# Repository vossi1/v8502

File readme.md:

# V8502 - Replacement for a 8502 with a 6502  

**Copyright (c) 2024 Vossi - v.1**

**www.mos6502.net**

## License
This work is licensed under a Creative Commons Attribution-ShareAlike 4.0
International License. See [https://creativecommons.org/licenses/by-sa/4.0/](https://creativecommons.org/licenses/by-sa/4.0/).

v.1 initial (base is V6510 v.3)

**[Schematic](https://github.com/vossi1/v8502/blob/master/v8502_v1.png)**

**[Parts](https://github.com/vossi1/v8502/blob/master/parts.txt)**

**CPLD-Firmware:** The .JED file can be uploaded with a JTAG-SMT2 Xilinx programmer (China) and [xc3sprog](https://xc3sprog.sourceforge.net/)

:exclamation: **BEWARE: I got good CPLD's from China, but there are some XC9572XL FAKES out there!**

:white_check_mark: **Tested successfully  with a UMC 6502A in my C128 & C128D-CR::**

- Risen from the Oblivion VIC
- Risen from the Oblivion VDC
- CPM VIC mode
- CPM VDC 80 column mode
- GEOS VIC mode with REU 1764, Mouse
- GEOS VDC mode with REU 1764, Mouse
- C128 Diagnostic cartridge
- Elite 128
- Sonic with REU 1764 c64 mode
- Galaxian cartridge C64 mode
- Blue Max from disk C64 mode
- Basic lesson loaded from tape
- SD2IEC with FB64 & FB128

**For a WDC 65C02 you have to cut the small trace in the other solder jumper.**

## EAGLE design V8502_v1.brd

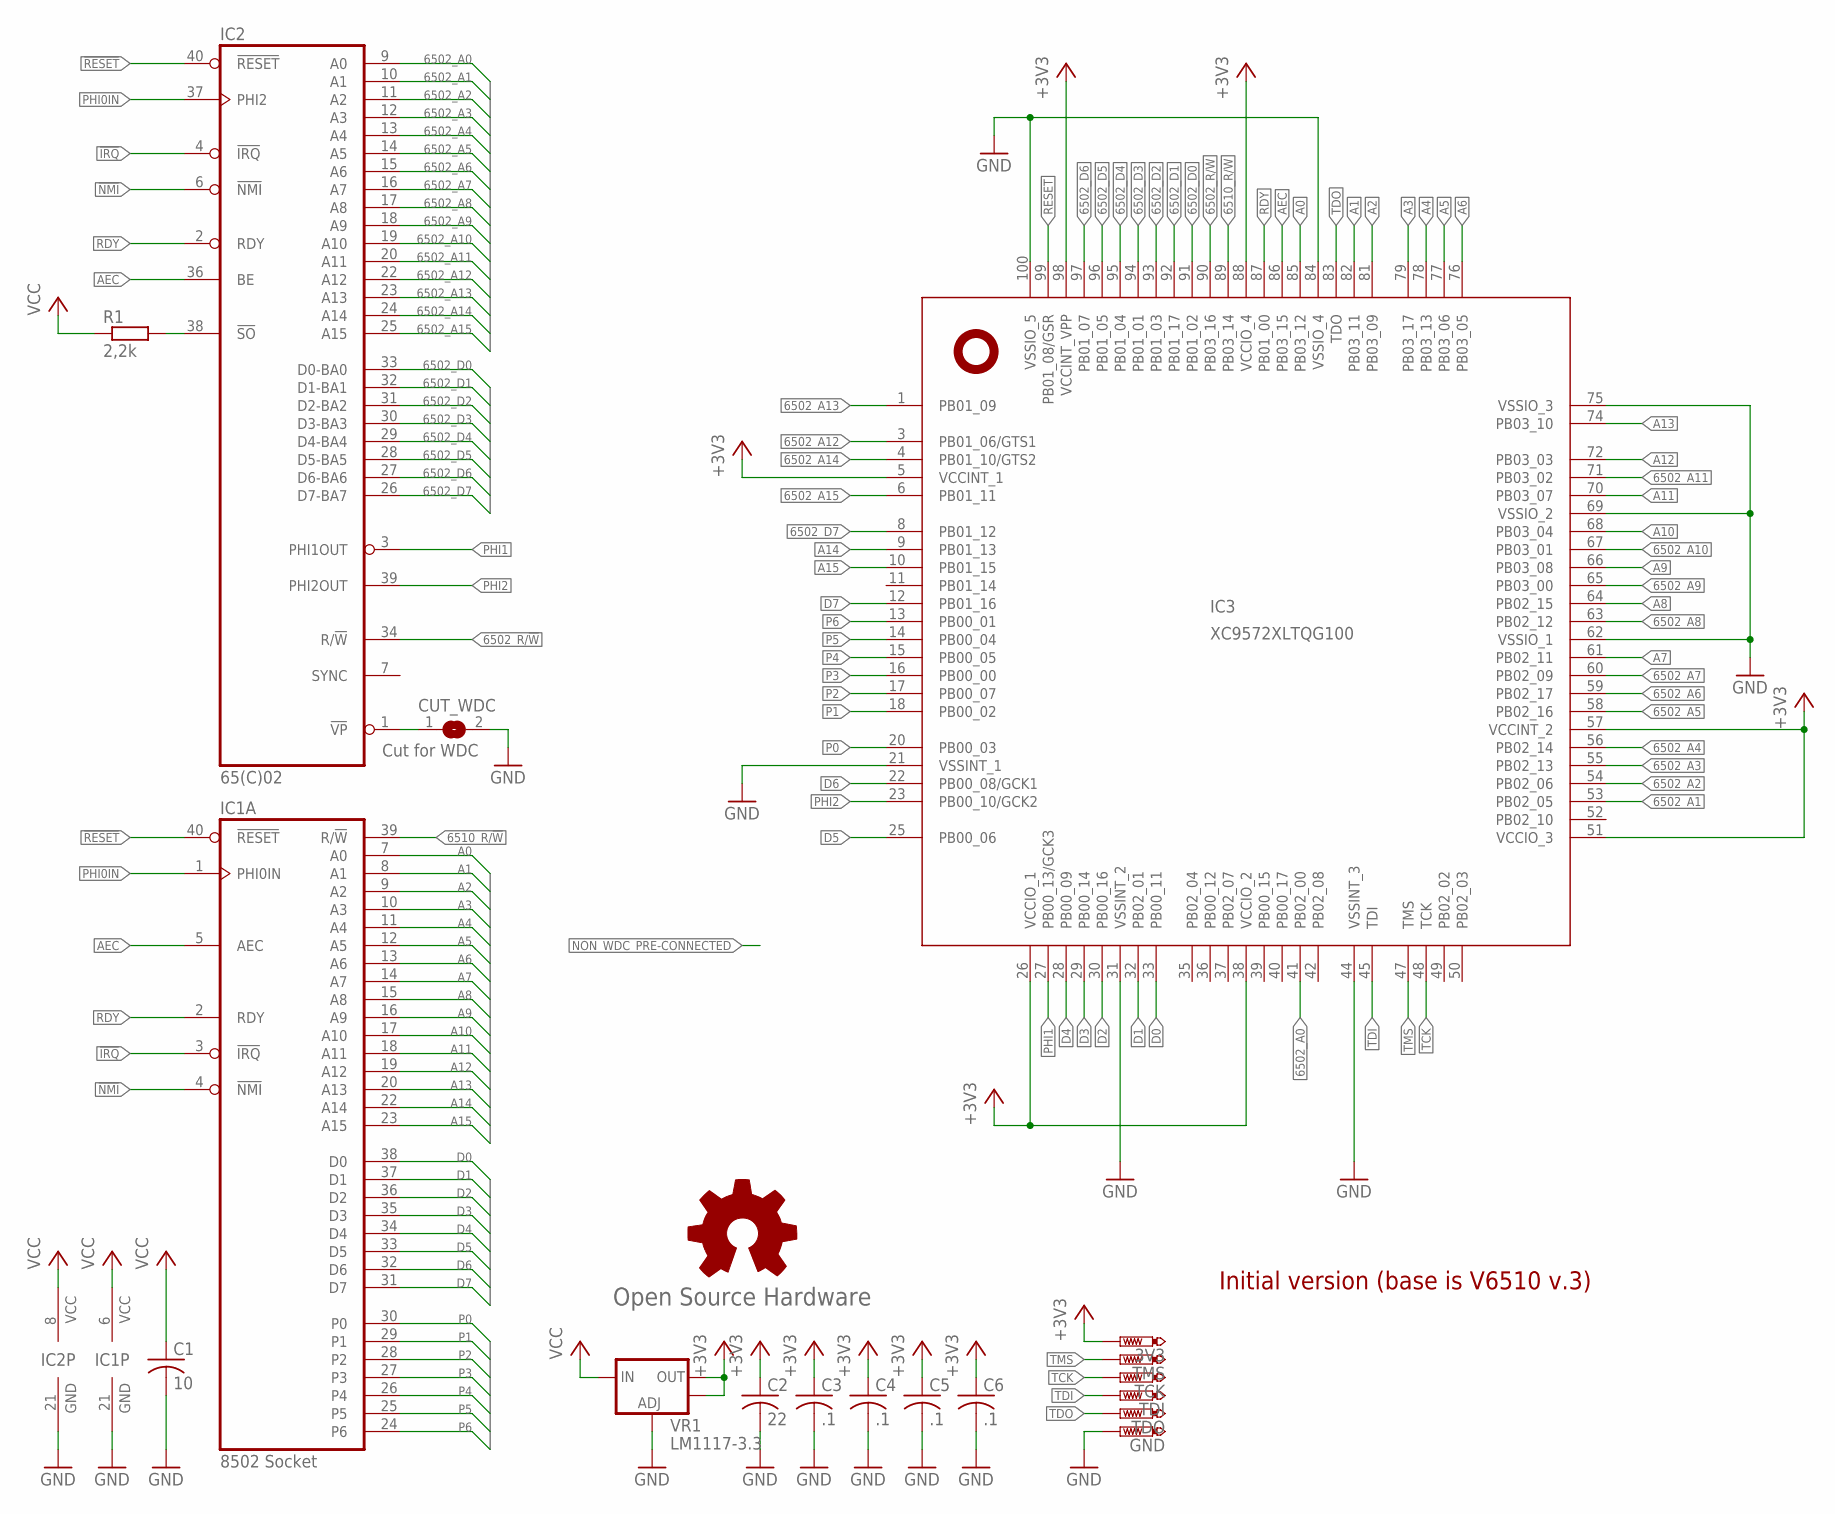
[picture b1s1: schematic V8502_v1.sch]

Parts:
3V3: PTR1TP08R; TP08R
C1: 10; C0805
C2: 22; C0805
C3, C4, C5, C6: .1; C0603
CUT_WDC: Cut for WDC; SJ
GND: PTR1TP08R; TP08R
GOLD_ORB_SM1: Open Source Hardware; OSHW_5MM
IC1: 8502 Socket; DIL40-ROUNDPAD
IC2: 65(C)02; DIL40-ROUNDPAD
IC3: XC9572XLTQG100; TQFP100
R1: 2,2k; 0603
TCK: PTR1TP08R; TP08R
TDI: PTR1TP08R; TP08R
TDO: PTR1TP08R; TP08R
TMS: PTR1TP08R; TP08R
VR1: LM1117-3.3; SOT223

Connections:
6502_A0: IC2.9 (A0), IC3.41 (PB02_00)
6502_A1: IC2.10 (A1), IC3.53 (PB02_05)
6502_A2: IC2.11 (A2), IC3.54 (PB02_06)
6502_A3: IC2.12 (A3), IC3.55 (PB02_13)
6502_A4: IC2.13 (A4), IC3.56 (PB02_14)
6502_A5: IC2.14 (A5), IC3.58 (PB02_16)
6502_A6: IC2.15 (A6), IC3.59 (PB02_17)
6502_A7: IC2.16 (A7), IC3.60 (PB02_09)
6502_A8: IC2.17 (A8), IC3.63 (PB02_12)
6502_A9: IC2.18 (A9), IC3.65 (PB03_00)
6502_A10: IC2.19 (A10), IC3.67 (PB03_01)
6502_A11: IC2.20 (A11), IC3.71 (PB03_02)
6502_A12: IC2.22 (A12), IC3.3 (PB01_06/GTS1)
6502_A13: IC2.23 (A13), IC3.1 (PB01_09)
6502_A14: IC2.24 (A14), IC3.4 (PB01_10/GTS2)
6502_A15: IC2.25 (A15), IC3.6 (PB01_11)
6502_D0: IC2.33 (D0-BA0), IC3.91 (PB01_02)
6502_D1: IC2.32 (D1-BA1), IC3.92 (PB01_17)
6502_D2: IC2.31 (D2-BA2), IC3.93 (PB01_03)
6502_D3: IC2.30 (D3-BA3), IC3.94 (PB01_01)
6502_D4: IC2.29 (D4-BA4), IC3.95 (PB01_04)
6502_D5: IC2.28 (D5-BA5), IC3.96 (PB01_05)
6502_D6: IC2.27 (D6-BA6), IC3.97 (PB01_07)
6502_D7: IC2.26 (D7-BA7), IC3.8 (PB01_12)
6502_R/!W: IC2.34 (R/!W), IC3.90 (PB03_16)
6502_VSS: CUT_WDC.1, IC2.1 (!VP)
6510_R/!W: IC1.39 (R/!W), IC3.89 (PB03_14)
!IRQ: IC1.3 (!IRQ), IC2.4 (!IRQ)
!NMI: IC1.4 (!NMI), IC2.6 (!NMI)
!RESET: IC1.40 (!RESET), IC2.40 (!RESET), IC3.99 (PB01_08/GSR)
!SO: IC2.38 (!SO), R1.2
+3V3: 3V3.TP, C2.1, C3.1, C4.1, C5.1, C6.1, IC3.5 (VCCINT_1), IC3.26 (VCCIO_1), IC3.38 (VCCIO_2), IC3.51 (VCCIO_3), IC3.57 (VCCINT_2), IC3.88 (VCCIO_4), IC3.98 (VCCINT_VPP), VR1.2 (OUT), VR1.4 (OUT)
A0: IC1.7 (A0), IC3.85 (PB03_12)
A1: IC1.8 (A1), IC3.82 (PB03_11)
A2: IC1.9 (A2), IC3.81 (PB03_09)
A3: IC1.10 (A3), IC3.79 (PB03_17)
A4: IC1.11 (A4), IC3.78 (PB03_13)
A5: IC1.12 (A5), IC3.77 (PB03_06)
A6: IC1.13 (A6), IC3.76 (PB03_05)
A7: IC1.14 (A7), IC3.61 (PB02_11)
A8: IC1.15 (A8), IC3.64 (PB02_15)
A9: IC1.16 (A9), IC3.66 (PB03_08)
A10: IC1.17 (A10), IC3.68 (PB03_04)
A11: IC1.18 (A11), IC3.70 (PB03_07)
A12: IC1.19 (A12), IC3.72 (PB03_03)
A13: IC1.20 (A13), IC3.74 (PB03_10)
A14: IC1.22 (A14), IC3.9 (PB01_13)
A15: IC1.23 (A15), IC3.10 (PB01_15)
AEC: IC1.5 (AEC), IC2.36 (BE), IC3.86 (PB03_15)
D0: IC1.38 (D0), IC3.33 (PB00_11)
D1: IC1.37 (D1), IC3.32 (PB02_01)
D2: IC1.36 (D2), IC3.30 (PB00_16)
D3: IC1.35 (D3), IC3.29 (PB00_14)
D4: IC1.34 (D4), IC3.28 (PB00_09)
D5: IC1.33 (D5), IC3.25 (PB00_06)
D6: IC1.32 (D6), IC3.22 (PB00_08/GCK1)
D7: IC1.31 (D7), IC3.12 (PB01_16)
GND: C1.2, C2.2, C3.2, C4.2, C5.2, C6.2, CUT_WDC.2, GND.TP, IC1.21 (GND), IC2.21 (GND), IC3.21 (VSSINT_1), IC3.31 (VSSINT_2), IC3.44 (VSSINT_3), IC3.62 (VSSIO_1), IC3.69 (VSSIO_2), IC3.75 (VSSIO_3), IC3.84 (VSSIO_4), IC3.100 (VSSIO_5), VR1.1 (ADJ)
P0: IC1.30 (P0), IC3.20 (PB00_03)
P1: IC1.29 (P1), IC3.18 (PB00_02)
P2: IC1.28 (P2), IC3.17 (PB00_07)
P3: IC1.27 (P3), IC3.16 (PB00_00)
P4: IC1.26 (P4), IC3.15 (PB00_05)
P5: IC1.25 (P5), IC3.14 (PB00_04)
P6: IC1.24 (P6), IC3.13 (PB00_01)
PHI0IN: IC1.1 (PHI0IN), IC2.37 (PHI2)
PHI1: IC2.3 (PHI1OUT), IC3.27 (PB00_13/GCK3)
PHI2: IC2.39 (PHI2OUT), IC3.23 (PB00_10/GCK2)
RDY: IC1.2 (RDY), IC2.2 (RDY), IC3.87 (PB01_00)
TCK: IC3.48 (TCK), TCK.TP
TDI: IC3.45 (TDI), TDI.TP
TDO: IC3.83 (TDO), TDO.TP
TMS: IC3.47 (TMS), TMS.TP
VCC: C1.1, IC1.6 (VCC), IC2.8 (VCC), R1.1, VR1.3 (IN)

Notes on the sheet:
Initial version (base is V6510 v.3)

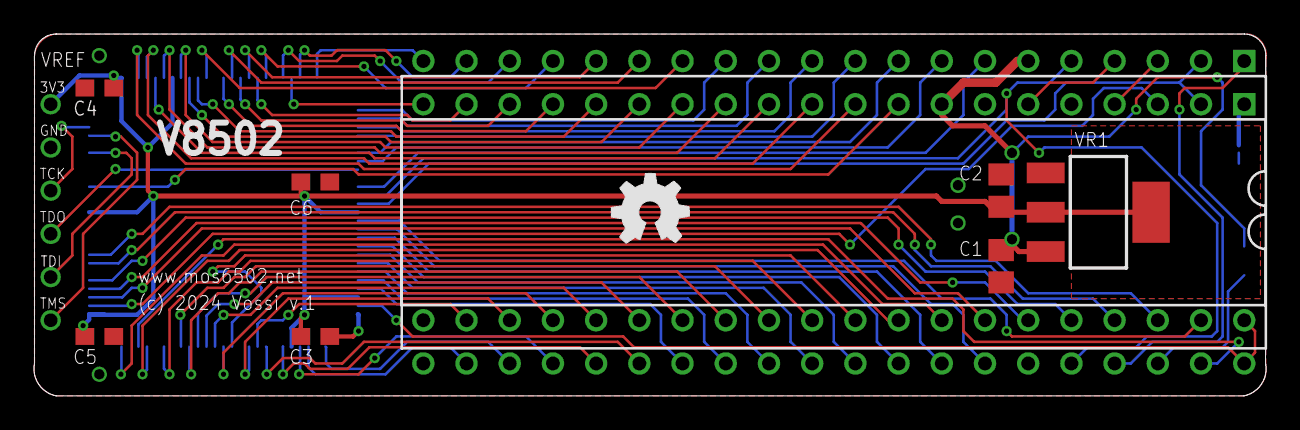
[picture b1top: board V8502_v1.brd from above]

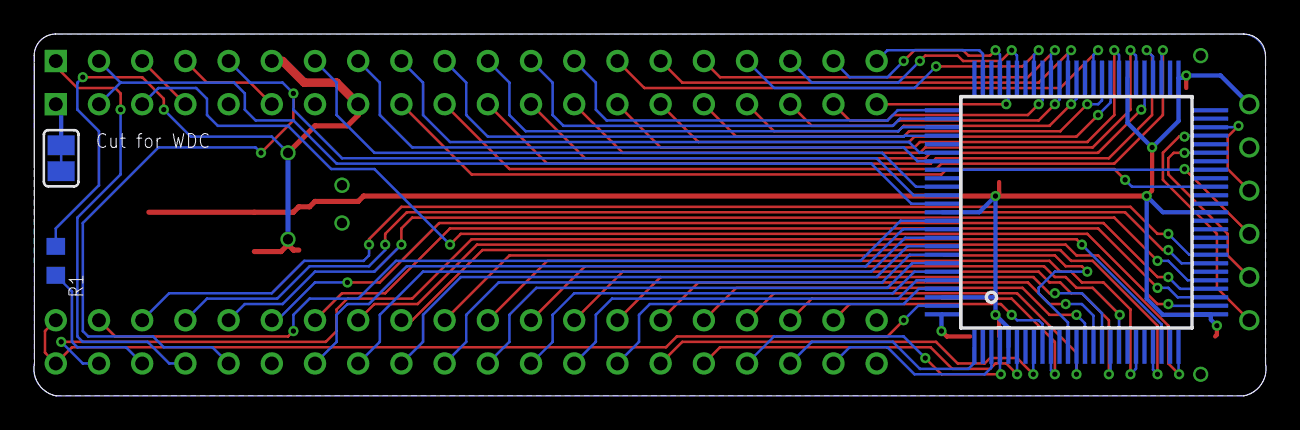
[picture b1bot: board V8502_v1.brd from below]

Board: 2 copper layers, 72.4 x 21.3 mm, 19 parts (3 on the bottom side), 74 nets.

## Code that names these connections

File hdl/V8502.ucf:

#NET "rdy"  LOC = "P87"  ; 

#PACE: Start of Constraints generated by PACE

#PACE: Start of PACE I/O Pin Assignments
NET "_reset"  LOC = "P99"  ; 
NET "address_6502<0>"  LOC = "P41"  ; 
NET "address_6502<10>"  LOC = "P67"  ; 
NET "address_6502<11>"  LOC = "P71"  ; 
NET "address_6502<12>"  LOC = "P3"  ; 
NET "address_6502<13>"  LOC = "P1"  ; 
NET "address_6502<14>"  LOC = "P4"  ; 
NET "address_6502<15>"  LOC = "P6"  ; 
NET "address_6502<1>"  LOC = "P53"  ; 
NET "address_6502<2>"  LOC = "P54"  ; 
NET "address_6502<3>"  LOC = "P55"  ; 
NET "address_6502<4>"  LOC = "P56"  ; 
NET "address_6502<5>"  LOC = "P58"  ; 
NET "address_6502<6>"  LOC = "P59"  ; 
NET "address_6502<7>"  LOC = "P60"  ; 
NET "address_6502<8>"  LOC = "P63"  ; 
NET "address_6502<9>"  LOC = "P65"  ; 
NET "address_8502<0>"  LOC = "P85"  ; 
NET "address_8502<10>"  LOC = "P68"  ; 
NET "address_8502<11>"  LOC = "P70"  ; 
NET "address_8502<12>"  LOC = "P72"  ; 
NET "address_8502<13>"  LOC = "P74"  ; 
NET "address_8502<14>"  LOC = "P9"  ; 
NET "address_8502<15>"  LOC = "P10"  ; 
NET "address_8502<1>"  LOC = "P82"  ; 
NET "address_8502<2>"  LOC = "P81"  ; 
NET "address_8502<3>"  LOC = "P79"  ; 
NET "address_8502<4>"  LOC = "P78"  ; 
NET "address_8502<5>"  LOC = "P77"  ; 
NET "address_8502<6>"  LOC = "P76"  ; 
NET "address_8502<7>"  LOC = "P61"  ; 
NET "address_8502<8>"  LOC = "P64"  ; 
NET "address_8502<9>"  LOC = "P66"  ; 
NET "aec"  LOC = "P86"  ; 
NET "data_6502<0>"  LOC = "P91"  ; 
NET "data_6502<1>"  LOC = "P92"  ; 
NET "data_6502<2>"  LOC = "P93"  ; 
NET "data_6502<3>"  LOC = "P94"  ; 
NET "data_6502<4>"  LOC = "P95"  ; 
NET "data_6502<5>"  LOC = "P96"  ; 
NET "data_6502<6>"  LOC = "P97"  ; 
NET "data_6502<7>"  LOC = "P8"  ; 
NET "data_8502<0>"  LOC = "P33"  ; 
NET "data_8502<1>"  LOC = "P32"  ; 
NET "data_8502<2>"  LOC = "P30"  ; 
NET "data_8502<3>"  LOC = "P29"  ; 
NET "data_8502<4>"  LOC = "P28"  ; 
NET "data_8502<5>"  LOC = "P25"  ; 
NET "data_8502<6>"  LOC = "P22"  ; 
NET "data_8502<7>"  LOC = "P12"  ;
NET "ioport<0>"  LOC = "P20"  ;
NET "ioport<1>"  LOC = "P18"  ;
NET "ioport<2>"  LOC = "P17"  ;
NET "ioport<3>"  LOC = "P16"  ;
NET "ioport<4>"  LOC = "P15"  ;
NET "ioport<5>"  LOC = "P14"  ;
NET "ioport<6>"  LOC = "P13"  ;
NET "phi1"  LOC = "P27"  ; 
NET "phi2"  LOC = "P23"  ; 
NET "r_w_6502"  LOC = "P90"  ; 
NET "r_w_8502"  LOC = "P89"  ; 

#PACE: Start of PACE Area Constraints

#PACE: Start of PACE Prohibit Constraints

#PACE: End of Constraints generated by PACE

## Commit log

2024-04-12 initial version - currently untested
2024-06-07 removed jlcjljlc
2024-06-20 license cc4
2024-07-03 now tested and working
2024-07-16 tests with reu1764, Mouse, c128 standard, jiffy
2025-01-10 added eagle files
2025-01-10 added firmware programming doc

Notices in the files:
parts and their libraries:
SparkFun: Licensing: CC v3.0 Share-Alike You are welcome to use this library for commercial purposes.
